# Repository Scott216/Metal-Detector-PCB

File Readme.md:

Matchless Metal Detector design is from Silicon Chip magazine June 2002.  
You can purchase circuit board from [OSH Park](http://oshpark.com/shared_projects/C76DDtcE)  
Instructions are here: 
http://www.geotech1.com/pages/metdet/projects/matchless/matchless300c.pdf

04106021

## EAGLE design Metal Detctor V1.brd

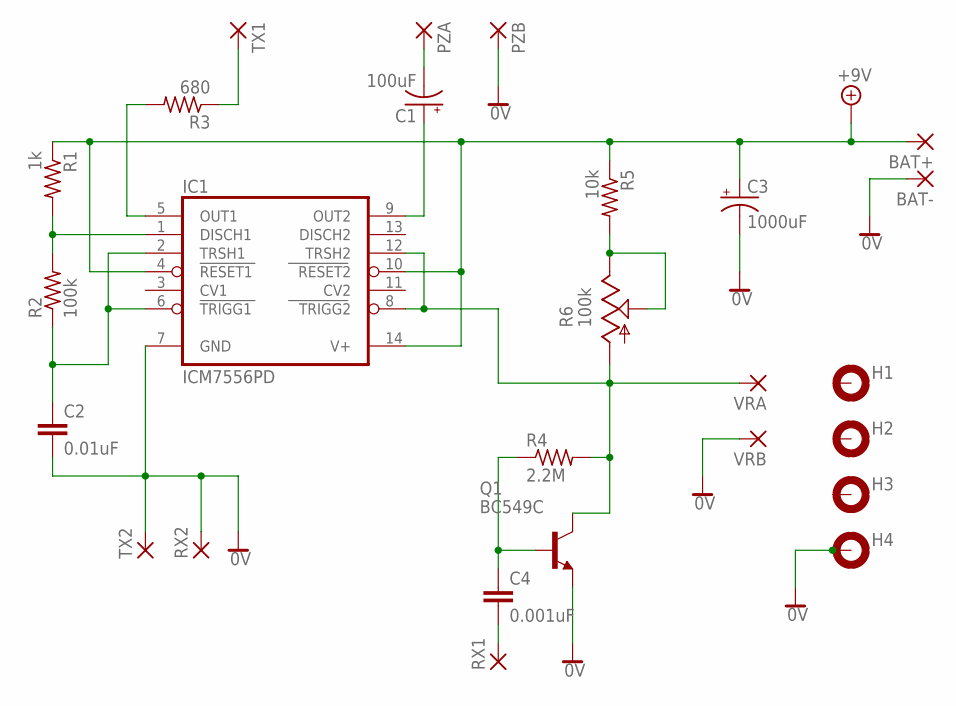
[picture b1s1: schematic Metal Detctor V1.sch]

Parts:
BAT+: WIREPAD2,54/1,1; 2,54/1,1
BAT-: WIREPAD2,54/1,1; 2,54/1,1
C1: 100uF; E5-8,5
C2: 0.01uF; C050-024X044
C3: 1000uF; E5-10,5
C4: 0.001uF; C050-024X044
H1, H2, H3, H4: MOUNT-PAD-ROUND3.0; 3,0-PAD
IC1: ICM7556PD; DIL14
PZA: WIREPAD2,54/1,1; 2,54/1,1
PZB: WIREPAD2,54/1,1; 2,54/1,1
Q1: BC549C; TO92-EBC
R1: 1k; 0207/12
R2: 100k; 0207/12
R3: 680; 0207/12
R4: 2.2M; 0207/12
R5: 10k; 0207/12
R6: 100k; SP19L
RX1, RX2: WIREPAD2,54/1,1; 2,54/1,1
TX1, TX2: WIREPAD2,54/1,1; 2,54/1,1
VRA: WIREPAD2,54/1,1; 2,54/1,1
VRB: WIREPAD2,54/1,1; 2,54/1,1

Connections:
0V: BAT-.1, C2.2, C3.-, H4.B3,0, IC1.7 (GND), PZB.1, Q1.E, RX2.1, TX2.1, VRB.1
+9V: BAT+.1, C3.+, IC1.4 (RESET1), IC1.10 (RESET2), IC1.14 (V+), R1.1, R5.1
unnamed: IC1.1 (DISCH1), R1.2, R2.2
unnamed: C2.1, IC1.2 (TRSH1), IC1.6 (TRIGG1), R2.1
unnamed: C1.+, IC1.9 (OUT2)
unnamed: IC1.5 (OUT1), R3.2
unnamed: R3.1, TX1.1
unnamed: IC1.8 (TRIGG2), IC1.12 (TRSH2), Q1.C, R4.2, R6.A, VRA.1
unnamed: C4.1, Q1.B, R4.1
unnamed: R5.2, R6.E, R6.S
unnamed: C1.-, PZA.1
unnamed: C4.2, RX1.1

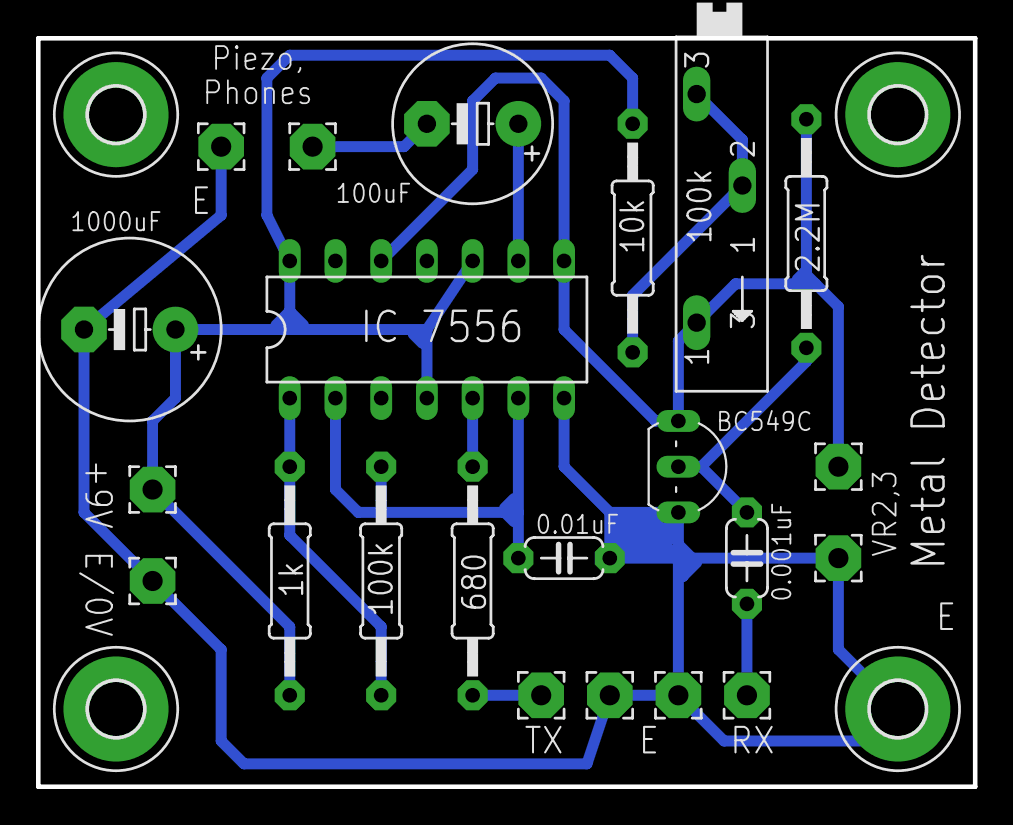
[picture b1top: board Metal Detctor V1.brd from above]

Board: 2 copper layers, 52.0 x 41.6 mm, 26 parts (0 on the bottom side), 12 nets.

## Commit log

2014-01-16 Added link to PDF Instructions
2014-01-16 Minor change
2014-01-16 Formatting
